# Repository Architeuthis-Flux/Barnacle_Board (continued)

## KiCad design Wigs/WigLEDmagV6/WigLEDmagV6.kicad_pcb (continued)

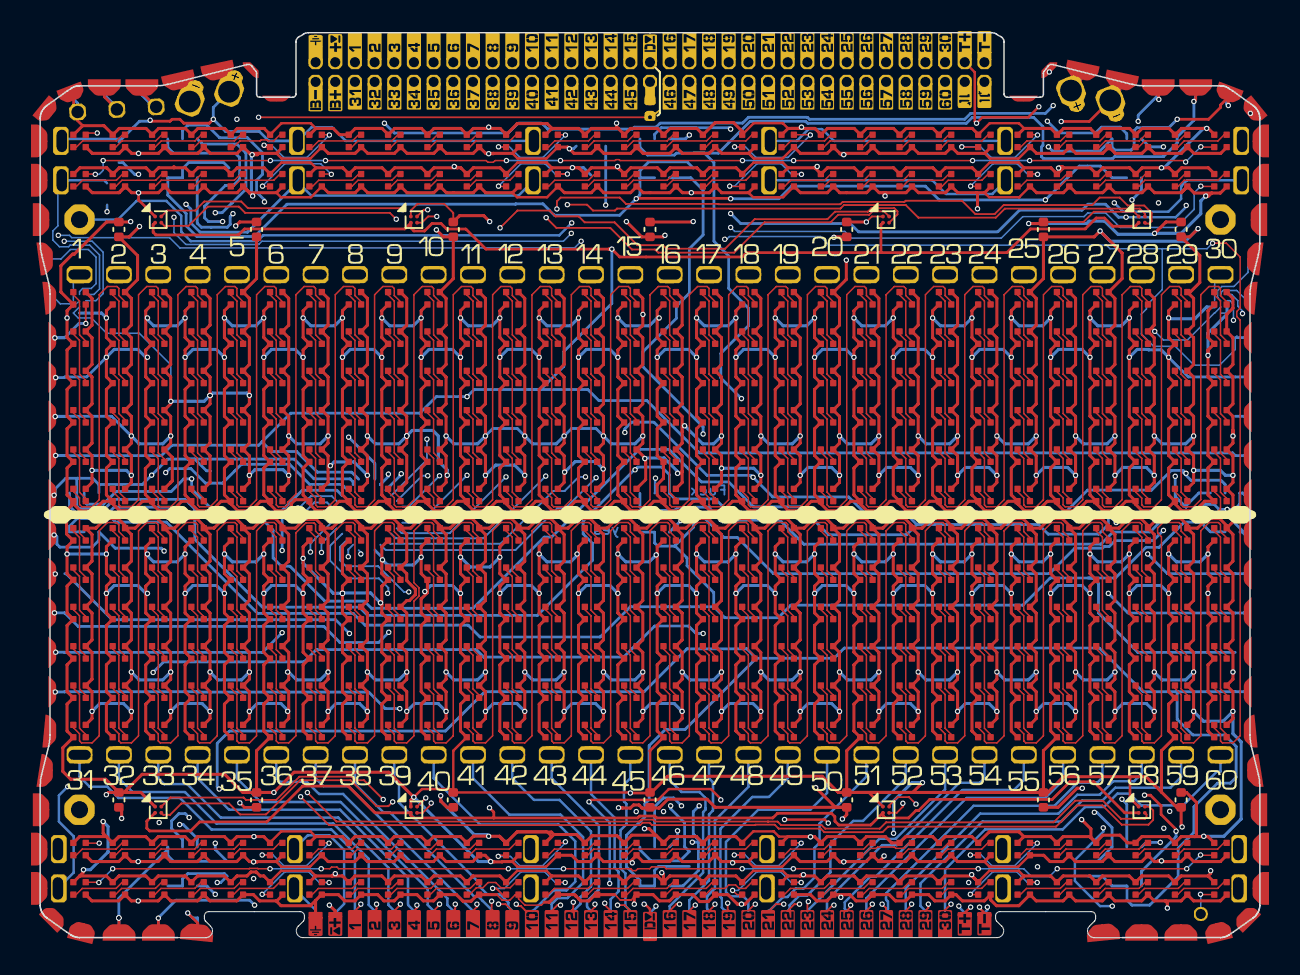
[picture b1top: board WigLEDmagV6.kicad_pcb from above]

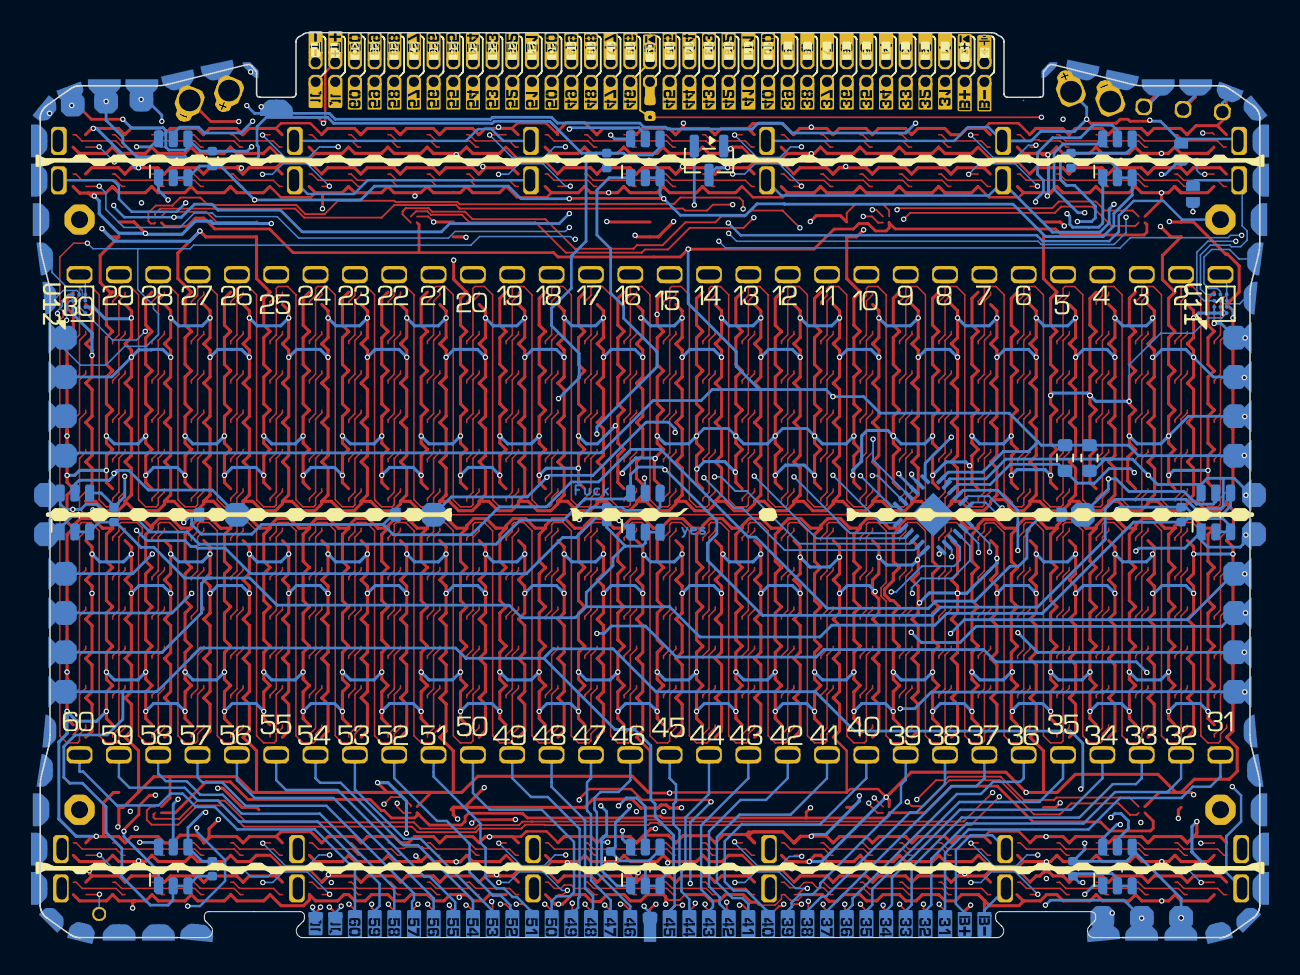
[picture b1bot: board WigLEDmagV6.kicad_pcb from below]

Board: 4 copper layers, 78.7 x 58.4 mm, 573 parts (56 on the bottom side), 587 nets.

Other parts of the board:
J1#2: SENSE_60; HEE70LP03BK_NumberedPads_CardGuide
TP19#2: TestPoint; TestPoint_Pad_D1.0mm

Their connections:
MVCC_2: TP19#2.1 (1_1); also elsewhere on the board

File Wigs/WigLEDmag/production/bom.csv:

Designator,Footprint,Quantity,Value,LCSC Part #
"_5, _4, _3, _2, ",,5,,
"C1, C10, C11, C12, C13, C14, C2, C3, C4, C5, C6, C7, C8, C9",0402,14,1uF,
"C15, C16, C17, C18, C19, C20, C21, C22, C23",0402,9,0.1uF,
"D101, D102, D103, D104, D105, D106, D11, D111, D112, D113, D114, D115, D116, D12, D121, D122, D123, D124, D125, D126, D13, D131, D132, D133, D134, D135, D136, D14, D141, D142, D143, D144, D145, D146, D15, D151, D152, D153, D154, D155, D156, D16, D161, D162, D163, D164, D165, D166, D171, D172, D173, D174, D175, D176, D181, D182, D183, D184, D185, D186, D191, D192, D193, D194, D195, D196, D201, D202, D203, D204, D205, D206, D21, D211, D212, D213, D214, D215, D216, D22, D221, D222, D223, D224, D225, D226, D23, D231, D232, D233, D234, D235, D236, D24, D241, D242, D243, D244, D245, D246, D25, D251, D252, D253, D254, D255, D256, D26, D261, D262, D263, D264, D265, D266, D271, D272, D273, D274, D275, D276, D281, D282, D283, D284, D285, D286, D291, D292, D293, D294, D295, D296, D301, D302, D303, D304, D305, D306, D31, D311, D312, D313, D314, D315, D316, D32, D321, D322, D323, D324, D325, D326, D33, D331, D332, D333, D334, D335, D336, D34, D341, D342, D343, D344, D345, D346, D35, D351, D352, D353, D354, D355, D356, D36, D361, D362, D363, D364, D365, D366, D371, D372, D373, D374, D375, D376, D381, D382, D383, D384, D385, D386, D391, D392, D393, D394, D395, D396, D401, D402",WS2812B-1313,200,WS2812B,C5349953
"D403, D404, D405, D406, D41, D411, D412, D413, D414, D415, D416, D42, D421, D422, D423, D424, D425, D426, D43, D431, D432, D433, D434, D435, D436, D44, D441, D442, D443, D444, D445, D446, D45, D451, D452, D453, D454, D455, D456, D46, D461, D462, D463, D464, D465, D466, D471, D472, D473, D474, D475, D476, D481, D482, D483, D484, D485, D486, D491, D492, D493, D494, D495, D496, D501, D502, D503, D504, D505, D506, D51, D511, D512, D513, D514, D515, D516, D52, D521, D522, D523, D524, D525, D526, D53, D531, D532, D533, D534, D535, D536, D54, D541, D542, D543, D544, D545, D546, D55, D551, D552, D553, D554, D555, D556, D56, D561, D562, D563, D564, D565, D566, D571, D572, D573, D574, D575, D576, D581, D582, D583, D584, D585, D586, D591, D592, D593, D594, D595, D596, D601, D602, D603, D604, D605, D606, D61, D611, D6110, D6111, D6112, D6113, D6114, D6115, D6116, D6117, D6118, D6119, D612, D6120, D6121, D6122, D6123, D6124, D6125, D6126, D6127, D6128, D6129, D613, D6130, D614, D615, D616, D617, D618, D619, D62, D621, D6210, D6211, D6212, D6213, D6214, D6215, D6216, D6217, D6218, D6219, D622, D6220, D6221, D6222, D6223, D6224, D6225, D6226, D6227, D6228, D6229, D623, D6230, D624, D625, D626, D627, D628, D629, D63, D631",WS2812B-1313,200,WS2812B,C5349953
"D6310, D6311, D6312, D6313, D6314, D6315, D6316, D6317, D6318, D6319, D632, D6320, D6321, D6322, D6323, D6324, D6325, D6326, D6327, D6328, D6329, D633, D6330, D634, D635, D636, D637, D638, D639, D64, D641, D6410, D6411, D6412, D6413, D6414, D6415, D6416, D6417, D6418, D6419, D642, D6420, D6421, D6422, D6423, D6424, D6425, D6426, D6427, D6428, D6429, D643, D6430, D644, D645, D646, D647, D648, D649, D65, D66, D71, D72, D73, D74, D75, D76, D81, D82, D83, D84, D85, D86, D91, D92, D93, D94, D95, D96",WS2812B-1313,80,WS2812B,C5349953
J1_2,Conn_1x1_SenseRiser,1,SENSE_60,
J1,HEE70LP03BK_NumberedPads_CardGuide,1,SENSE_60,
"J10, J8",Banana_Minus_sm,2,Conn_01x01,
J11,Breadboard_6NonHoles,1,~,
"J12, J13",fulledge_gap,2,Conn_01x32,
"J14, J15, J16",PinHeader_1x1_Smallest,3,Conn_01x01,
J2,PinHeader_2x35_P1.27_wiig_card,1,Barnacle_Connector_70pin,
J3,SideConnect_sparserrr_Bottom_tighter,1,Barnacle_Connector_70pin,
J4,Conn_1x1_SenseRiser,1,SENSE_1,
J5,Conn_1x1_SenseRiser,1,SENSE_30,
J6,Conn_1x1_SenseRiser,1,SENSE_31,
"J7, J9",Banana_Plus_sm,2,Conn_01x01,
"JP1, JP2",SolderJumper_2_Open_Small,2,Jumper_2_Open,
"JP3, JP4, JP5",SolderJumper_2_Bridged_Small,3,M~{INT},
"M51, M52, M53, M54, M55, M56, M57, M58, M59",SOT-23-6_TMAG5273,9,~,
"R1, R2",0603,2,4.7K,
"TP10, TP11, TP12, TP14, TP15, TP16, TP17, TP18, TP19_2, TP19, TP20, TP21, TP22, TP23, TP24, TP27, TP28, TP29, TP4, TP5, TP6, TP7, TP8, TP9",TestPoint_Pad_D1.0mm,24,TestPoint,
TP3,PinHeader_1x1_0.6mm_tinyAF,1,LED OUT,
U1,VQFN-24-1EP_4x4mm_P0.5mm_EP2.45x2.45mm,1,TCA9548APWR,C555456
"U10, U2, U4, U5, U6, U7, U8, U9",WLP-4_0.86x0.86mm_P0.4mm,8,MMC5603NJL,
"U11, U12",Maxim_WLP-12_2.008x1.608mm_Layout4x3_P0.4mm,2,~,
U3,SOT-23,1,AP2127N-3.3,

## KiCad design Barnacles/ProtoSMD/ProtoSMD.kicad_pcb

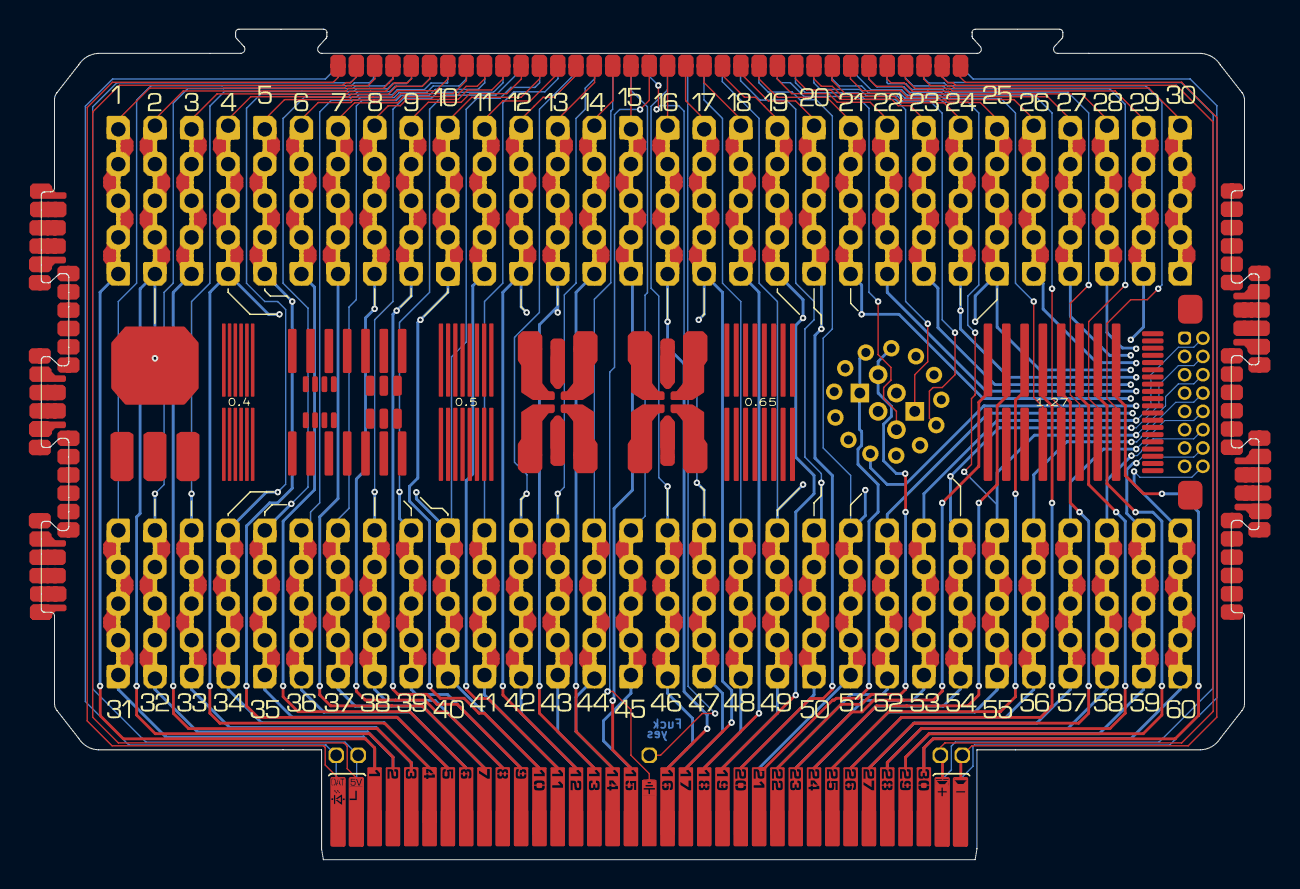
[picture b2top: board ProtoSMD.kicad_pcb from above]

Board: 2 copper layers, 84.5 x 57.6 mm, 26 parts (0 on the bottom side), 70 nets.

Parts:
J1, J2, J3, J4, J5: Conn_01x01; PinHeader_1x1_Smallest
J1#2: Conn_01x01; HEE70LP03BK_NumberedPads_CardGuide
J6: Conn_01x01; SideConnect_sparserrr_Bottom_drawing
J11, J18: Conn_01x30; Conn_5x30_breadboard_sin_passives
J12: Conn_01x30; SideConnect_short_right_Drawing
J13: Conn_02x30_Top_Bottom; SideConnect_short_left_Drawing
J15: Conn_02x08_Counter_Clockwise; Lines_P1.27_16
J16: Conn_02x08_Counter_Clockwise; Lines_P0.65_16
J19: Conn_02x08_Counter_Clockwise; Lines_P0.5_16
J20: Conn_02x06_Counter_Clockwise; Lines_P0.4_12
J21: Conn_02x07_Counter_Clockwise; SOIC14_SOT23-8-6
J22: Conn_02x03_Counter_Clockwise; SOT-223
J25, J26: Conn_01x03_Pin; TO-92
J27, J28: Conn_02x03_Counter_Clockwise; LED_6_SMD
J29: Conn_02x08_Counter_Clockwise; PinHeader_2x08_P1.27mm_Vertical
J30: Conn_02x10_Counter_Clockwise; FPC FC05-S20FCT
J65: Conn_2Rows-13Pins; nixies-us-IN-16
U1: HEE70LP03BK_CardSide
U3: SideConnect_sparserrr_Top

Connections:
1: J18.1, J20.1, U1.1, U3.1
2: J18.2, J20.2, J22.4, U1.2, U3.2
3: J18.3, J20.3, U1.3, U3.3
4: J18.4, J20.4, J21.1, U1.4, U3.4
5: J18.5, J20.5, J21.2, U1.5, U3.5
6: J18.6, J20.6, J21.3, U1.6, U3.6
7: J18.7, J19.1, J21.4, U1.7, U3.7
8: J18.8, J19.2, J21.5, U1.8, U3.8
9: J18.9, J19.3, J21.6, U1.9, U3.9
10: J18.10, J19.4, J21.7, U1.10, U3.10
11: J18.11, J19.5, U1.11, U3.11
12: J18.12, J19.6, J27.3, U1.12, U3.12
13: J18.13, J19.7, J27.2, U1.13, U3.13
14: J18.14, J19.8, J27.1, U1.14, U3.14
15: J16.1, J18.15, J28.3, U1.15, U3.15
16: J16.2, J18.16, J28.2, U1.16, U3.16
17: J16.3, J18.17, J28.1, U1.17, U3.17
18: J16.4, J18.18, U1.18, U3.18
19: J16.5, J18.19, J65.1, U1.19, U3.19
20: J16.6, J18.20, J65.2, U1.20, U3.20
21: J16.7, J18.21, J25.1, J30.1, J65.3, U1.21, U3.21
22: J16.8, J18.22, J25.2, J30.2, J65.4, U1.22, U3.22
23: J15.1, J18.23, J25.3, J29.1, J30.3, J65.5, U1.23, U3.23
24: J15.2, J18.24, J29.2, J30.4, J65.6, U1.24, U3.24
25: J15.3, J18.25, J29.3, J30.5, J65.7, U1.25, U3.25
26: J15.4, J18.26, J29.4, J30.6, U1.26, U3.26
27: J15.5, J18.27, J29.5, J30.7, U1.27, U3.27
28: J15.6, J18.28, J29.6, J30.8, U1.28, U3.28
29: J15.7, J18.29, J29.7, J30.9, U1.29, U3.29
30: J15.8, J18.30, J29.8, J30.10, U1.30, U3.30
31: J11.1, J20.12, J22.1, U1.31, U3.31
32: J11.2, J20.11, J22.2, U1.32 (Pin_0), U3.32 (Pin_0)
33: J11.3, J20.10, J22.3, U1.33 (Pin_1), U3.33 (Pin_1)
34: J11.4, J20.9, J21.14, U1.34 (Pin_2), U3.34 (Pin_2)
35: J11.5, J20.8, J21.13, U1.35 (Pin_3), U3.35 (Pin_3)
36: J11.6, J20.7, J21.12, U1.36 (Pin_4), U3.36 (Pin_4)
37: J11.7, J19.16, J21.11, U1.37 (Pin_5), U3.37 (Pin_5)
38: J11.8, J19.15, J21.10, U1.38 (Pin_6), U3.38 (Pin_6)
39: J11.9, J19.14, J21.9, U1.39 (Pin_7), U3.39 (Pin_7)
40: J11.10, J19.13, J21.8, U1.40 (Pin_8), U3.40 (Pin_8)
41: J11.11, J19.12, U1.41 (Pin_9), U3.41 (Pin_9)
42: J11.12, J19.11, J27.4, U1.42 (Pin_10), U3.42 (Pin_10)
43: J11.13, J19.10, J27.5, U1.43 (Pin_11), U3.43 (Pin_11)
44: J11.14, J19.9, J27.6, U1.44 (Pin_12), U3.44 (Pin_12)
45: J11.15, J16.16, J28.4, U1.45 (Pin_13), U3.45 (Pin_13)
46: J11.16, J16.15, J28.5, U1.46 (Pin_14), U3.46 (Pin_14)
47: J11.17, J16.14, J28.6, U1.47 (Pin_15), U3.47 (Pin_15)
48: J11.18, J16.13, U1.48 (Pin_16), U3.48 (Pin_16)
49: J11.19, J16.12, J65.13, U1.49 (Pin_17), U3.49 (Pin_17)
50: J11.20, J16.11, J65.12, U1.50 (Pin_18), U3.50 (Pin_18)
51: J11.21, J16.10, J26.3, J30.20, J65.11, U1.51 (Pin_19), U3.51 (Pin_19)
52: J11.22, J16.9, J26.2, J30.19, J65.10, U1.52 (Pin_20), U3.52 (Pin_20)
53: J11.23, J15.16, J26.1, J29.16, J30.18, J65.9, U1.53 (Pin_21), U3.53 (Pin_21)
54: J11.24, J15.15, J29.15, J30.17, J65.8, U1.54 (Pin_22), U3.54 (Pin_22)
55: J11.25, J15.14, J29.14, J30.16, U1.55 (Pin_23), U3.55 (Pin_23)
56: J11.26, J15.13, J29.13, J30.15, U1.56 (Pin_24), U3.56 (Pin_24)
57: J11.27, J15.12, J29.12, J30.14, U1.57 (Pin_25), U3.57 (Pin_25)
58: J11.28, J15.11, J29.11, J30.13, U1.58 (Pin_26), U3.58 (Pin_26)
59: J11.29, J15.10, J29.10, J30.12, U1.59 (Pin_27), U3.59 (Pin_27)
60: J11.30, J15.9, J29.9, J30.11, U1.60 (Pin_28), U3.60 (Pin_28)
BOT_RAIL_NEG: J4.1, U1.64 (Bot_Neg), U3.64 (Bot_Neg)
BOT_RAIL_POS: J3.1, U1.63 (Bot_Pos), U3.63 (Bot_Pos)
GND: U1.68 (GND), U3.68 (GND)
LED_5V: U1.70 (LED_5V), U3.70 (LED_5V)
LED_DAT: U1.69 (LED_Data), U3.69 (LED_Data)
PASS: J5.1, U1.65 (Center), U3.65 (Center)
SENSE_BOTTOM: U1.67 (PadSense_Bottom), U3.67 (PadSense_Bottom)
SENSE_TOP: U1.66 (PadSense_Top), U3.66 (PadSense_Top)
TOP_RAIL_NEG: J2.1, U1.62 (Top_Neg), U3.62 (Top_Neg)
TOP_RAIL_POS: J1.1, U1.61 (Top_Pos), U3.61 (Top_Pos)

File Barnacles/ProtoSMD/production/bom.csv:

Designator,Footprint,Quantity,Value,LCSC Part #
"J1_2, J2, J3, J4, J5",PinHeader_1x1_Smallest,5,Conn_01x01,
J1,HEE70LP03BK_NumberedPads_CardGuide,1,Conn_01x01,
"J11, J18",Conn_5x30_breadboard_sin_passives,2,Conn_01x30,
J12,SideConnect_short_right_Drawing,1,Conn_01x30,
J13,SideConnect_short_left_Drawing,1,Conn_02x30_Top_Bottom,
J15,Lines_P1.27_16,1,Conn_02x08_Counter_Clockwise,
J16,Lines_P0.65_16,1,Conn_02x08_Counter_Clockwise,
J19,Lines_P0.5_16,1,Conn_02x08_Counter_Clockwise,
J20,Lines_P0.4_12,1,Conn_02x06_Counter_Clockwise,
J21,SOIC14_SOT23-8-6,1,Conn_02x07_Counter_Clockwise,
J22,SOT-223,1,Conn_02x03_Counter_Clockwise,
"J25, J26",TO-92,2,Conn_01x03_Pin,
"J27, J28",LED_6_SMD,2,Conn_02x03_Counter_Clockwise,C5349953
J29,PinHeader_2x08_P1.27mm_Vertical,1,Conn_02x08_Counter_Clockwise,
J30,FPC FC05-S20FCT,1,Conn_02x10_Counter_Clockwise,
J6,SideConnect_sparserrr_Bottom_drawing,1,Conn_01x01,
J65,nixies-us-IN-16,1,Conn_2Rows-13Pins,
U1,HEE70LP03BK_CardSide,1,~,
U3,SideConnect_sparserrr_Top,1,~,

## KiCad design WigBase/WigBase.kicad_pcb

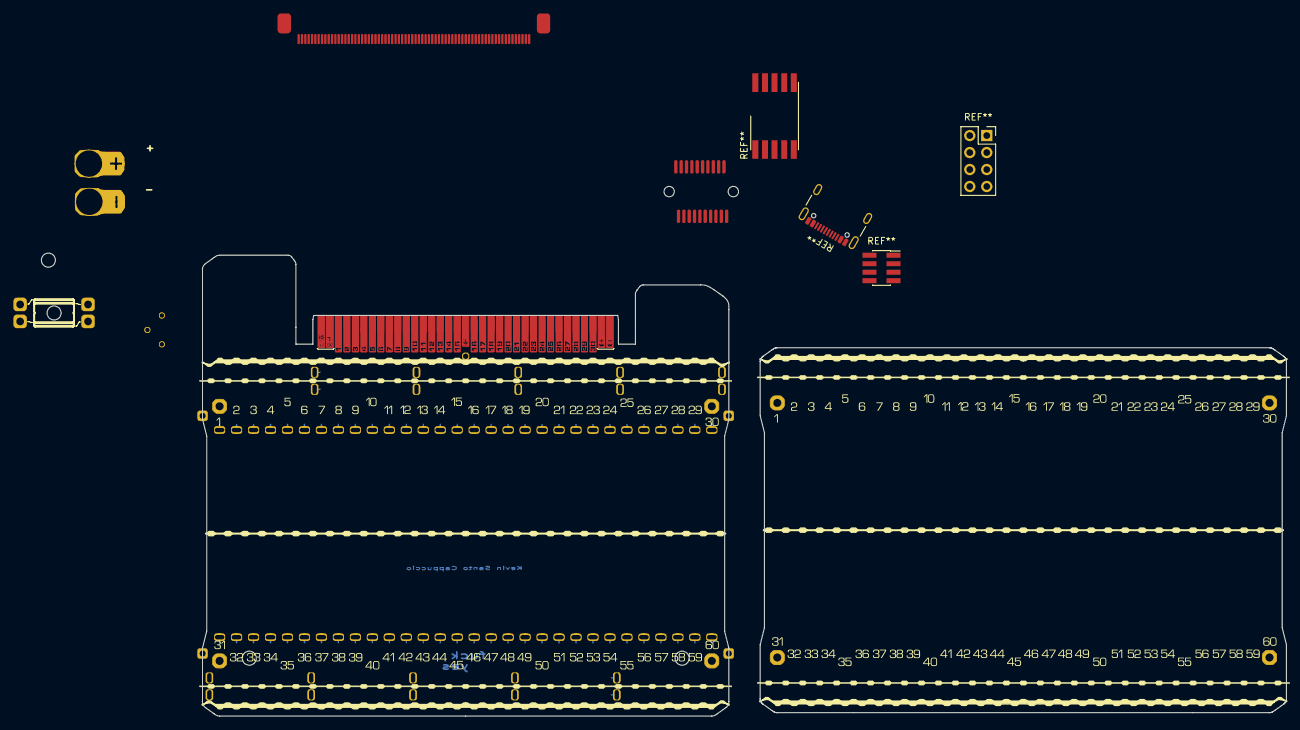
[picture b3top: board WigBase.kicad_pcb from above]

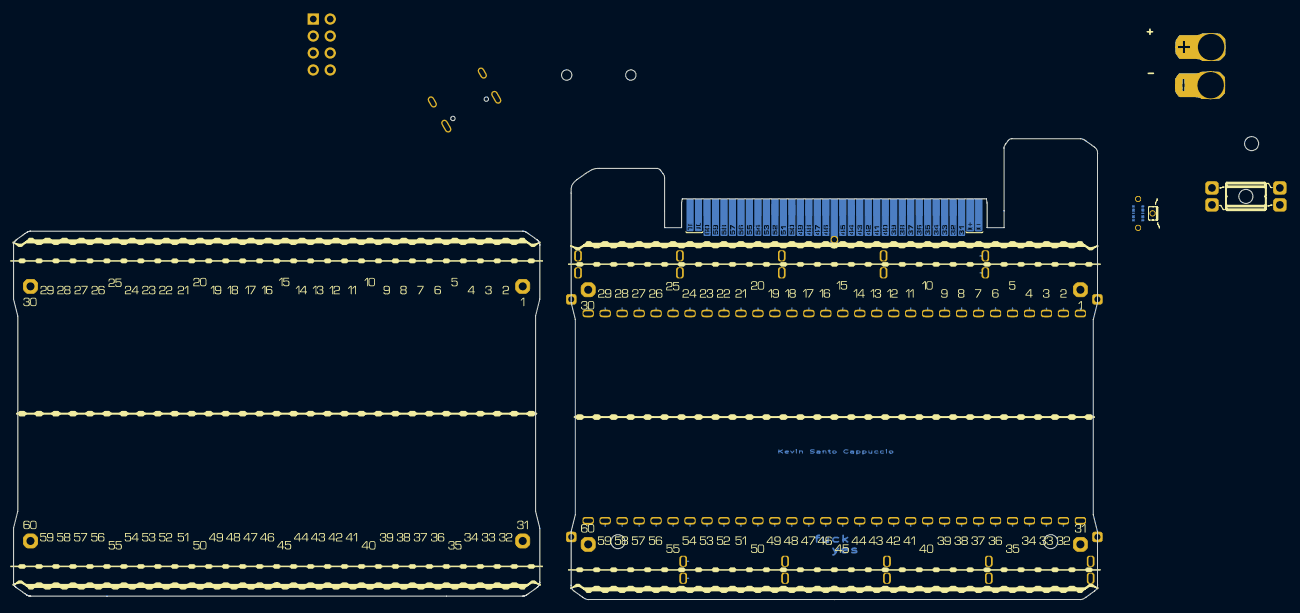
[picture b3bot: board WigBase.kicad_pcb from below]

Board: 2 copper layers, 162.2 x 69.0 mm, 18 parts (4 on the bottom side), 71 nets, no tracks yet.

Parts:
J1: Conn_02x35_Top_Bottom; HEE70LP03BK_NumberedPads_symm
J1#2: Conn_02x35_Top_Bottom; HEE70LP03BK_NumberedPads_CardGuide
J2: pad_sense_1; PinHeader_1x1_Smaller
J3: pad_sense_30; PinHeader_1x1_Smaller
J4: pad_sense_60; PinHeader_1x1_Smaller
J5: pad_sense_31; PinHeader_1x1_Smaller
J11: Connector_Breadboard; Breadboard_6NonHoles
J14: Conn_01x06; GT-B0353FSV06-02B0201
J15: Conn_01x01; PinHeader_1x1_Smallest
TP16: LED DIN; PinHeader_1x1_0.6mm_tinyAF
TP18: LED 5V; PinHeader_1x1_0.6mm_tinyAF
TP19: LED GND; PinHeader_1x1_0.6mm_tinyAF
TP24: TOP_POS_RAIL; Pad_Clip_Banana_PlusSmaller_topBottom
TP25: TOP_POS_RAIL; PINHEADER_Larger_Pad
TP26: TOP_NEG_RAIL; Pad_Clip_Banana_MinusSmaller_topBottom
TP27: TOP_NEG_RAIL; PINHEADER_Larger_Pad
TP29: BOTTOM_POS_RAIL; PINHEADER_Larger_Pad
TP31: BOTTOM_NEG_RAIL; PINHEADER_Larger_Pad

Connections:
1: J1.1, J11.1
2: J1.2, J11.2
3: J1.3, J11.3
4: J1.4, J11.4
5: J1.5, J11.5
6: J1.6, J11.6
7: J1.7, J11.7
8: J1.8, J11.8
9: J1.9, J11.9
10: J1.10, J11.10
11: J1.11, J11.11
12: J1.12, J11.12
13: J1.13, J11.13
14: J1.14, J11.14
15: J1.15, J11.15
16: J1.16, J11.16
17: J1.17, J11.17
18: J1.18, J11.18
19: J1.19, J11.19
20: J1.20, J11.20
21: J1.21, J11.21
22: J1.22, J11.22
23: J1.23, J11.23
24: J1.24, J11.24
25: J1.25, J11.25
26: J1.26, J11.26
27: J1.27, J11.27
28: J1.28, J11.28
29: J1.29, J11.29
30: J1.30, J11.30
31: J1.31, J11.31
32: J1.32, J11.32 (Pin_0)
33: J1.33, J11.33 (Pin_1)
34: J1.34, J11.34 (Pin_2)
35: J1.35, J11.35 (Pin_3)
36: J1.36, J11.36 (Pin_4)
37: J1.37, J11.37 (Pin_5)
38: J1.38, J11.38 (Pin_6)
39: J1.39, J11.39 (Pin_7)
40: J1.40, J11.40 (Pin_8)
41: J1.41, J11.41 (Pin_9)
42: J1.42, J11.42 (Pin_10)
43: J1.43, J11.43 (Pin_11)
44: J1.44, J11.44 (Pin_12)
45: J1.45, J11.45 (Pin_13)
46: J1.46, J11.46 (Pin_14)
47: J1.47, J11.47 (Pin_15)
48: J1.48, J11.48 (Pin_16)
49: J1.49, J11.49 (Pin_17)
50: J1.50, J11.50 (Pin_18)
51: J1.51, J11.51 (Pin_19)
52: J1.52, J11.52 (Pin_20)
53: J1.53, J11.53 (Pin_21)
54: J1.54, J11.54 (Pin_22)
55: J1.55, J11.55 (Pin_23)
56: J1.56, J11.56 (Pin_24)
57: J1.57, J11.57 (Pin_25)
58: J1.58, J11.58 (Pin_26)
59: J1.59, J11.59 (Pin_27)
60: J1.60, J11.60 (Pin_28)
BOT_RAIL_NEG: J1.64, J11.64 (Bot_Neg), TP31.1
BOT_RAIL_POS: J1.63, J11.63 (Bot_Pos), TP29.1
GND: J1.68, J14.4, J14.5, TP19.1
LED_5V: J1.70, J14.3, J14.6, TP18.1
LED_DAT: J1.69, J14.1, J14.2, TP16.1
unnamed: J3.1, J5.1
PASS: J1.65, J15.1
SENSE_BOTTOM: J1.67, J4.1
SENSE_TOP: J1.66, J2.1
TOP_RAIL_NEG: J1.62, J11.62 (Top_Neg), TP26.1, TP27.1
TOP_RAIL_POS: J1.61, J11.61 (Top_Pos), TP24.1, TP25.1

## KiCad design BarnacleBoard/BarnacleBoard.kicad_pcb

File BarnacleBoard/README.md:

# Barnacle Board
###### the breadboard you stick barnacles to

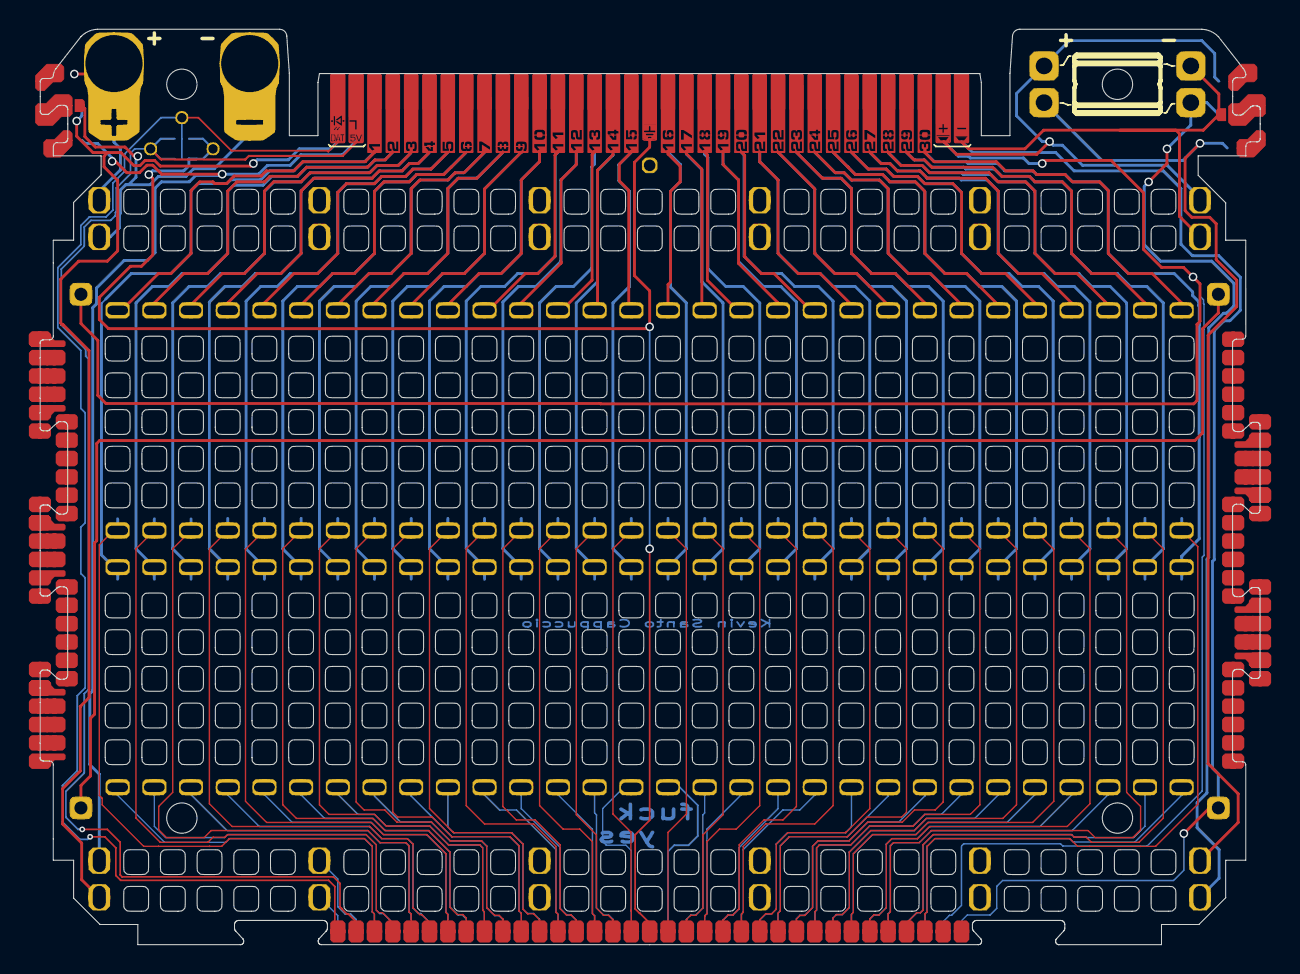
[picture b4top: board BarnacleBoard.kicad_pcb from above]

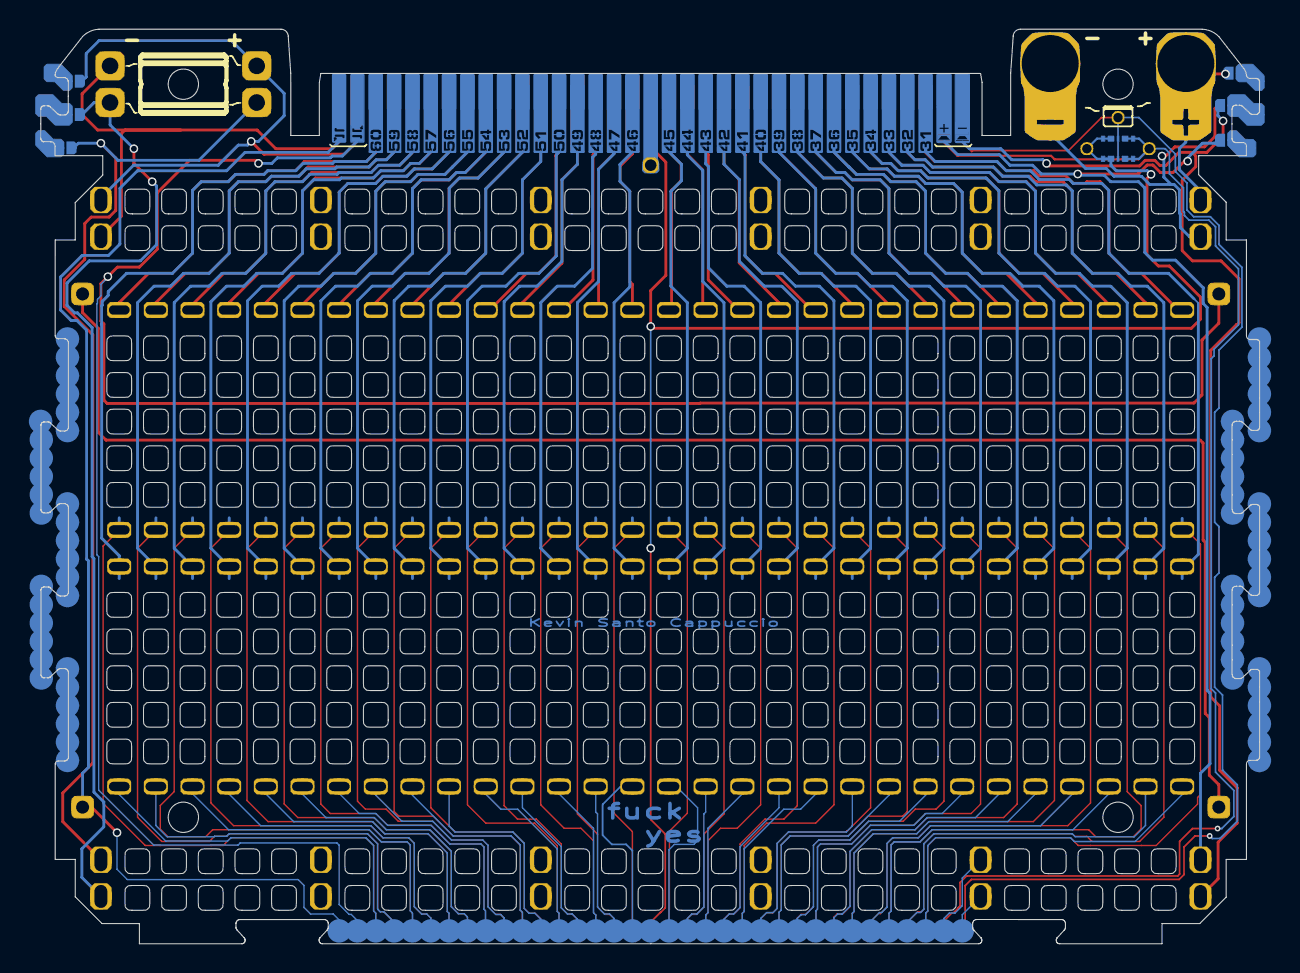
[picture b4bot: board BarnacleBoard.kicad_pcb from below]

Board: 2 copper layers, 84.5 x 63.4 mm, 28 parts (10 on the bottom side), 79 nets.

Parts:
J1: Conn_02x35_Top_Bottom; HEE70LP03BK_NumberedPads_symm
J2: pad_sense_1; PinHeader_1x1_Smaller
J3: pad_sense_30; PinHeader_1x1_Smaller
J4: pad_sense_60; PinHeader_1x1_Smaller
J5: pad_sense_31; PinHeader_1x1_Smaller
J6: Conn_02x35_Top_Bottom; SideConnect_sparserrr_Bottom
J11: Connector_Breadboard; Breadboard_CustomClips_CorrectPins_2
J12: Conn_02x03_Top_Bottom; SideConnect_short_right
J13: Conn_02x03_Top_Bottom; SideConnect_short_left
J14: Conn_01x06; GT-B0353FSV06-02B0201
J15: Conn_01x01; PinHeader_1x1_Smallest
JP3, JP4, JP5, JP6, JP7, JP8, JP9, JP10: SolderJumper_2_Open; SolderJumper_2_Open_Small
TP16: LED DIN; PinHeader_1x1_0.6mm_tinyAF
TP18: LED 5V; PinHeader_1x1_0.6mm_tinyAF
TP19: LED GND; PinHeader_1x1_0.6mm_tinyAF
TP24: TOP_POS_RAIL; Pad_Clip_Banana_PlusSmaller_topBottom
TP25: TOP_POS_RAIL; PINHEADER_Larger_Pad
TP26: TOP_NEG_RAIL; Pad_Clip_Banana_MinusSmaller_topBottom
TP27: TOP_NEG_RAIL; PINHEADER_Larger_Pad
TP29: BOTTOM_POS_RAIL; PINHEADER_Larger_Pad
TP31: BOTTOM_NEG_RAIL; PINHEADER_Larger_Pad

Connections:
1: J1.1, J6.1, J11.1
2: J1.2, J6.2, J11.2
3: J1.3, J6.3, J11.3
4: J1.4, J6.4, J11.4
5: J1.5, J6.5, J11.5
6: J1.6, J6.6, J11.6
7: J1.7, J6.7, J11.7
8: J1.8, J6.8, J11.8
9: J1.9, J6.9, J11.9
10: J1.10, J6.10, J11.10
11: J1.11, J6.11, J11.11
12: J1.12, J6.12, J11.12
13: J1.13, J6.13, J11.13
14: J1.14, J6.14, J11.14
15: J1.15, J6.15, J11.15
16: J1.16, J6.16, J11.16
17: J1.17, J6.17, J11.17
18: J1.18, J6.18, J11.18
19: J1.19, J6.19, J11.19
20: J1.20, J6.20, J11.20
21: J1.21, J6.21, J11.21
22: J1.22, J6.22, J11.22
23: J1.23, J6.23, J11.23
24: J1.24, J6.24, J11.24
25: J1.25, J6.25, J11.25
26: J1.26, J6.26, J11.26
27: J1.27, J6.27, J11.27
28: J1.28, J6.28, J11.28
29: J1.29, J6.29, J11.29
30: J1.30, J6.30, J11.30
31: J1.31, J6.31, J11.31
32: J1.32, J6.32, J11.32 (Pin_0)
33: J1.33, J6.33, J11.33 (Pin_1)
34: J1.34, J6.34, J11.34 (Pin_2)
35: J1.35, J6.35, J11.35 (Pin_3)
36: J1.36, J6.36, J11.36 (Pin_4)
37: J1.37, J6.37, J11.37 (Pin_5)
38: J1.38, J6.38, J11.38 (Pin_6)
39: J1.39, J6.39, J11.39 (Pin_7)
40: J1.40, J6.40, J11.40 (Pin_8)
41: J1.41, J6.41, J11.41 (Pin_9)
42: J1.42, J6.42, J11.42 (Pin_10)
43: J1.43, J6.43, J11.43 (Pin_11)
44: J1.44, J6.44, J11.44 (Pin_12)
45: J1.45, J6.45, J11.45 (Pin_13)
46: J1.46, J6.46, J11.46 (Pin_14)
47: J1.47, J6.47, J11.47 (Pin_15)
48: J1.48, J6.48, J11.48 (Pin_16)
49: J1.49, J6.49, J11.49 (Pin_17)
50: J1.50, J6.50, J11.50 (Pin_18)
51: J1.51, J6.51, J11.51 (Pin_19)
52: J1.52, J6.52, J11.52 (Pin_20)
53: J1.53, J6.53, J11.53 (Pin_21)
54: J1.54, J6.54, J11.54 (Pin_22)
55: J1.55, J6.55, J11.55 (Pin_23)
56: J1.56, J6.56, J11.56 (Pin_24)
57: J1.57, J6.57, J11.57 (Pin_25)
58: J1.58, J6.58, J11.58 (Pin_26)
59: J1.59, J6.59, J11.59 (Pin_27)
60: J1.60, J6.60, J11.60 (Pin_28)
BOT_RAIL_NEG: J1.64, J6.64, J11.64 (Bot_Neg), JP4.2 (B), JP8.2 (B), TP31.1
BOT_RAIL_POS: J1.63, J6.63, J11.63 (Bot_Pos), JP5.2 (B), JP9.2 (B), TP29.1
GND: J1.68, J6.68, J14.4, J14.5, TP19.1
LED_5V: J1.70, J6.70, J14.3, J14.6, TP18.1
LED_DAT: J1.69, J6.69, J14.1, J14.2, TP16.1
unnamed: J3.1, J5.1
unnamed: J12.1, J12.4, JP7.1 (A)
unnamed: J12.2, JP10.2 (B)
unnamed: J12.3, J12.6, JP9.1 (A)
unnamed: J12.5, JP8.1 (A)
unnamed: J13.1, J13.4, JP3.1 (A)
unnamed: J13.2, JP6.2 (B)
unnamed: J13.3, J13.6, JP5.1 (A)
unnamed: J13.5, JP4.1 (A)
PASS: J1.65, J6.65, J15.1
SENSE_BOTTOM: J1.67, J4.1, J6.67
SENSE_TOP: J1.66, J2.1, J6.66
TOP_RAIL_NEG: J1.62, J6.62, J11.62 (Top_Neg), JP6.1 (A), JP10.1 (A), TP26.1, TP27.1
TOP_RAIL_POS: J1.61, J6.61, J11.61 (Top_Pos), JP3.2 (B), JP7.2 (B), TP24.1, TP25.1

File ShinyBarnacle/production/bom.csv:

Designator,Footprint,Quantity,Value,LCSC Part #
J1,HEE70LP03BK_NumberedPads_symm,1,Conn_02x35_Top_Bottom,
J11,Breadboard_CustomClips_CorrectPins_2,1,Connector_Breadboard,
J12,SideConnect_short_right,1,Conn_02x03_Top_Bottom,
J13,SideConnect_short_left,1,Conn_02x03_Top_Bottom,
J14,GT-B0353FSV06-02B0201,1,Conn_01x06,
J15,PinHeader_1x1_Smallest,1,Conn_01x01,
J2,PinHeader_1x1_Smaller,1,pad_sense_1,
J3,PinHeader_1x1_Smaller,1,pad_sense_30,
J4,PinHeader_1x1_Smaller,1,pad_sense_60,
J5,PinHeader_1x1_Smaller,1,pad_sense_31,
J6,SideConnect_sparserrr_Bottom,1,Conn_02x35_Top_Bottom,
TP16,PinHeader_1x1_0.6mm_tinyAF,1,LED DIN,
TP18,PinHeader_1x1_0.6mm_tinyAF,1,LED 5V,
TP19,PinHeader_1x1_0.6mm_tinyAF,1,LED GND,
TP24,Pad_Clip_Banana_PlusSmaller_topBottom,1,TOP_POS_RAIL,
TP25,PINHEADER_Larger_Pad,1,TOP_POS_RAIL,
TP26,Pad_Clip_Banana_MinusSmaller_topBottom,1,TOP_NEG_RAIL,
TP27,PINHEADER_Larger_Pad,1,TOP_NEG_RAIL,
TP29,PINHEADER_Larger_Pad,1,BOTTOM_POS_RAIL,
TP31,PINHEADER_Larger_Pad,1,BOTTOM_NEG_RAIL,
